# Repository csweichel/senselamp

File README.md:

SenseLamp
============================

SenseLamp is a drop-in lampshade replacement that can remotely turn the light on and off, runs Linux, is WiFi connected and has a bunch of sensors:
 * __Temperature and humidity sensor:__ recommended DHT11/DHT12 or anything pin-compatible
 * __PIR motion sensor:__ typically HC-SR501 PIR, easily found on eBay
 * __LDR light sensor:__ any light-dependent resistor works as long as the voltage divider is adjusted

In addition to a custom PCB, the SenseLamp is powered by a [TL WR703N](http://wiki.openwrt.org/toh/tp-link/tl-wr703n) WiFi router, which can be bought for cheap of eBay. The total power consumption is around 120-150mA/5V.

## How does this thing look like?
Images can be found in my blog: [32leav.es](http://32leav.es/?tag=senselamp)

## What's in this repository?
 * <tt>board</tt> the [Eagle](http://www.cadsoftusa.com/) files for the custom PCB going on top of the WR703N
 * <tt>frame</tt> AutoDesk Inventor sources and DXF files for two laser cut frame variants. The RectangularFrame could be ordered from [Ponoko](https://www.ponoko.com/), while the AngeledFrame requires some advanced laser-cutting techniques.
 * <tt>msp430</tt> contains the firmware for the MSP430 controlling the sensors - written using [Energia](https://github.com/energia/Energia/)

## What is __NOT__ in this repository?
The OpenWRT user-land to actually speak with the sensors. I use SenseLamps in combination with [busfarhn](https://github.com/32leaves/busfahrn), and have some code there that might help: [scripts/native_clients](https://github.com/32leaves/busfahrn/tree/master/scripts/native_clients).

## How do I build my own?
1. Get all the parts: a TL-WR703N, a TI Launchpad incl. its MSP430G2553, all the sensors and parts needed for the board (see schematics) and some form of relay module.
2. Solder thin wires to the serial testpads of the WR703N - see existing sources how to do this: [here](http://forums.openpilot.org/blog/52/entry-92-unbrick-wr703n-wifi-router/), [here](http://www.designspark.com/blog/hacking-the-tp-link-tl-wr703n) and [here](http://www.instructables.com/id/TL-WR703N-serial-port/). In the end you should have two wires that you could solder onto the SenseLamp board.
3. Solder all components on the SenseLamp board.
4. Laser-cut a frame or go to town on some tupperware with a Dremel
5. Assemble all components onto the frame
6. Power the whole contraption and play with some commands (have a look at the firmware for what commands there are)
7. Hook it up to your busfarhn installation.

# License - "MIT License"
Copyright (c) 2013 Christian Weichel, 32leaves

Permission is hereby granted, free of charge, to any person obtaining a copy of this software and associated documentation files (the "Software"), to deal in the Software without restriction, including without limitation the rights to use, copy, modify, merge, publish, distribute, sublicense, and/or sell copies of the Software, and to permit persons to whom the Software is furnished to do so, subject to the following conditions:

The above copyright notice and this permission notice shall be included in all copies or substantial portions of the Software.

THE SOFTWARE IS PROVIDED "AS IS", WITHOUT WARRANTY OF ANY KIND, EXPRESS OR IMPLIED, INCLUDING BUT NOT LIMITED TO THE WARRANTIES OF MERCHANTABILITY, FITNESS FOR A PARTICULAR PURPOSE AND NONINFRINGEMENT. IN NO EVENT SHALL THE AUTHORS OR COPYRIGHT HOLDERS BE LIABLE FOR ANY CLAIM, DAMAGES OR OTHER LIABILITY, WHETHER IN AN ACTION OF CONTRACT, TORT OR OTHERWISE, ARISING FROM, OUT OF OR IN CONNECTION WITH THE SOFTWARE OR THE USE OR OTHER DEALINGS IN THE SOFTWARE.

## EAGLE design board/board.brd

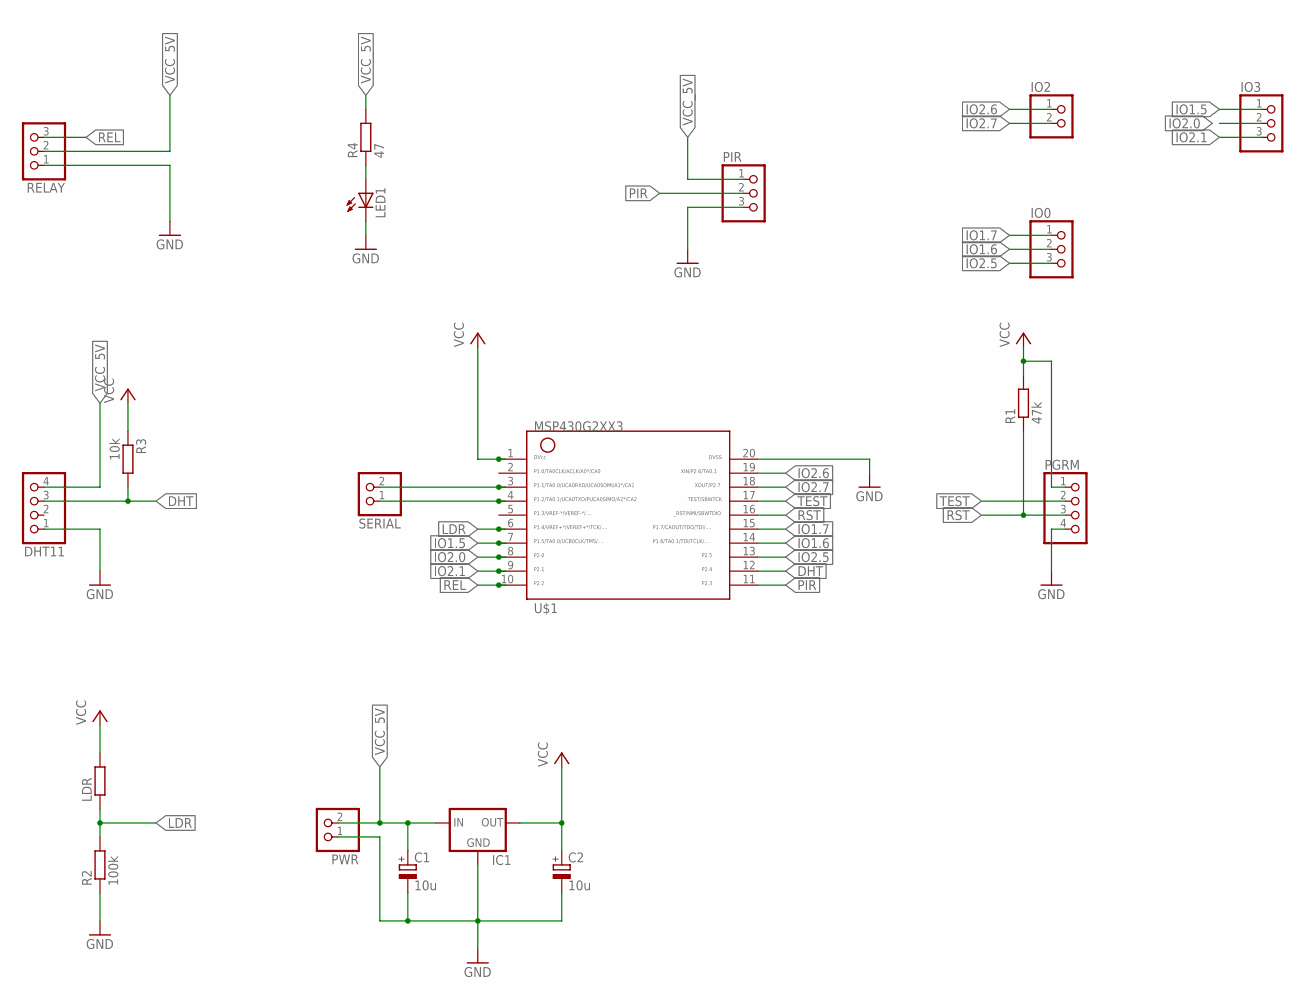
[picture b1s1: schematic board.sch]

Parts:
C1, C2: 10u; E2,5-5
DHT11: PINHD-1X4; 1X04
IC1: MCP1700TRI; TO92
IO0, IO3: PINHD-1X3; 1X03
IO2: PINHD-1X2; 1X02
LDR: R-EU_0207/5V; 0207/5V
LED1: LED3MM
PGRM: PINHD-1X4; 1X04
PIR: PINHD-1X3; 1X03
PWR: PINHD-1X2; 1X02
R1: 47k; 0207/10
R2: 100k; 0207/10
R3: 10k; 0207/10
R4: 47; 0207/10
RELAY: PINHD-1X3; 1X03
SERIAL: PINHD-1X2; 1X02
U$1: G2XX3---N20; N20

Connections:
DHT: DHT11.3, R3.2, U$1.12
GND: C1.-, C2.-, DHT11.1, IC1.1 (GND), LED1.K (C), PGRM.4, PIR.3, PWR.1, R2.1, RELAY.1, U$1.20
IO1.5: IO3.1, U$1.7
IO1.6: IO0.2, U$1.14
IO1.7: IO0.1, U$1.15
IO2.0: IO3.2, U$1.8
IO2.1: IO3.3, U$1.9
IO2.5: IO0.3, U$1.13
IO2.6: IO2.1, U$1.19
IO2.7: IO2.2, U$1.18
LDR: LDR.1, R2.2, U$1.6
unnamed: LED1.A, R4.1
unnamed: SERIAL.2, U$1.3
unnamed: SERIAL.1, U$1.4
PIR: PIR.2, U$1.11
REL: RELAY.3, U$1.10
RST: PGRM.3, R1.1, U$1.16
TEST: PGRM.2, U$1.17
VCC: C2.+, IC1.3 (OUT), LDR.2, PGRM.1, R1.2, R3.1, U$1.1
VCC_5V: C1.+, DHT11.4, IC1.2 (IN), PIR.1, PWR.2, R4.2, RELAY.2

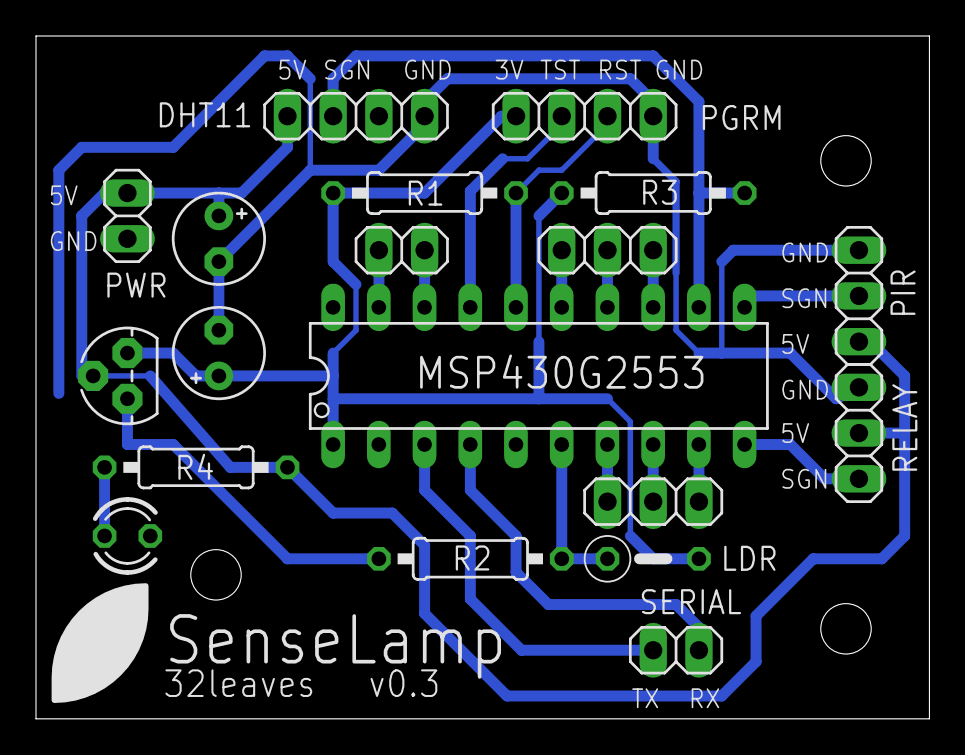
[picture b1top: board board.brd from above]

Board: 2 copper layers, 49.6 x 37.9 mm, 19 parts (0 on the bottom side), 20 nets.

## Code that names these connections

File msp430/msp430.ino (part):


#define PIN_RELAY 10
#define PIN_PIR   11
#define PIN_DHT   12
#define PIN_LDR   A4
#define LDR_AVG   10
//define NO_LED
#define NO_PREAMBLE
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  uint8_t j = 0, i;
  
  uint8_t data[6];
  uint8_t _pin = PIN_DHT;
  uint32_t _lastMillis;
  boolean _lastResult;
  uint32_t _temperature, _humidity;
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
int readDHTBytes(unsigned char* buffer) {
  // send start signal
  pinMode(PIN_DHT, OUTPUT);
  digitalWrite(PIN_DHT, HIGH);
  delay(250);
  digitalWrite(PIN_DHT, LOW);
  delay(18);
  digitalWrite(PIN_DHT, HIGH);
  delayMicroseconds(8);
  pinMode(PIN_DHT, INPUT);

  // wait for LOW response
  {
    int i = 0;
    while(digitalRead(PIN_DHT) == LOW) {
      if(i++ >= 8) return DHT_ERROR_TIMEOUT;
      delayMicroseconds(10);
    }
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  // wait for HIGH response
  {
    int i = 0;
    while(digitalRead(PIN_DHT) == HIGH) {
      if(i++ >= 8) return DHT_ERROR_TIMEOUT;
      delayMicroseconds(10);
    }
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    int bit = 0;
    for(bit = 0; bit < 8; bit++) {
      // wait until signal goes high
      while(digitalRead(PIN_DHT) != HIGH) nop();// delayMicroseconds(1);

      // if signal is still high, this bit is a 1
      delayMicroseconds(30);
      if(digitalRead(PIN_DHT) == HIGH) {
        buffer[bite] |= 1 << (7 - bit);
        while(digitalRead(PIN_DHT) != LOW) nop();//delayMicroseconds(1);
        //delayMicroseconds(10);
      }
    }
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void updateLDRReading() {
  unsigned long avg = 0;
  for(int i = 0; i < LDR_AVG; i++) {
    avg += analogRead(PIN_LDR);
  }
  Serial.print("LDR l:"); Serial.println(avg / LDR_AVG);
}
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  pinMode(PIN_RELAY, OUTPUT);
  digitalWrite(PIN_RELAY, HIGH);
  
  pinMode(PIN_PIR, INPUT);
  pinMode(PIN_DHT, OUTPUT);

  #ifndef NO_LED
  pinMode(LED_BOOT, OUTPUT);  
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    inByte = 0;
  }
  
  int newButtonState = digitalRead(PIN_PIR);
  if(careAboutPIR && newButtonState != buttonState && newButtonState == HIGH && abs(millis() - buttonDebounce) > 100) {
    Serial.print("PIR b:");
    Serial.print(newButtonState);
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
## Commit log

2013-03-13 fixed some space issues of the v0.1 board
2013-03-18 finished the v02 board
2013-03-31 updated the board and firmware to a new revision / pin mapping is now correct and installing a PIR sensor is a lot easier
